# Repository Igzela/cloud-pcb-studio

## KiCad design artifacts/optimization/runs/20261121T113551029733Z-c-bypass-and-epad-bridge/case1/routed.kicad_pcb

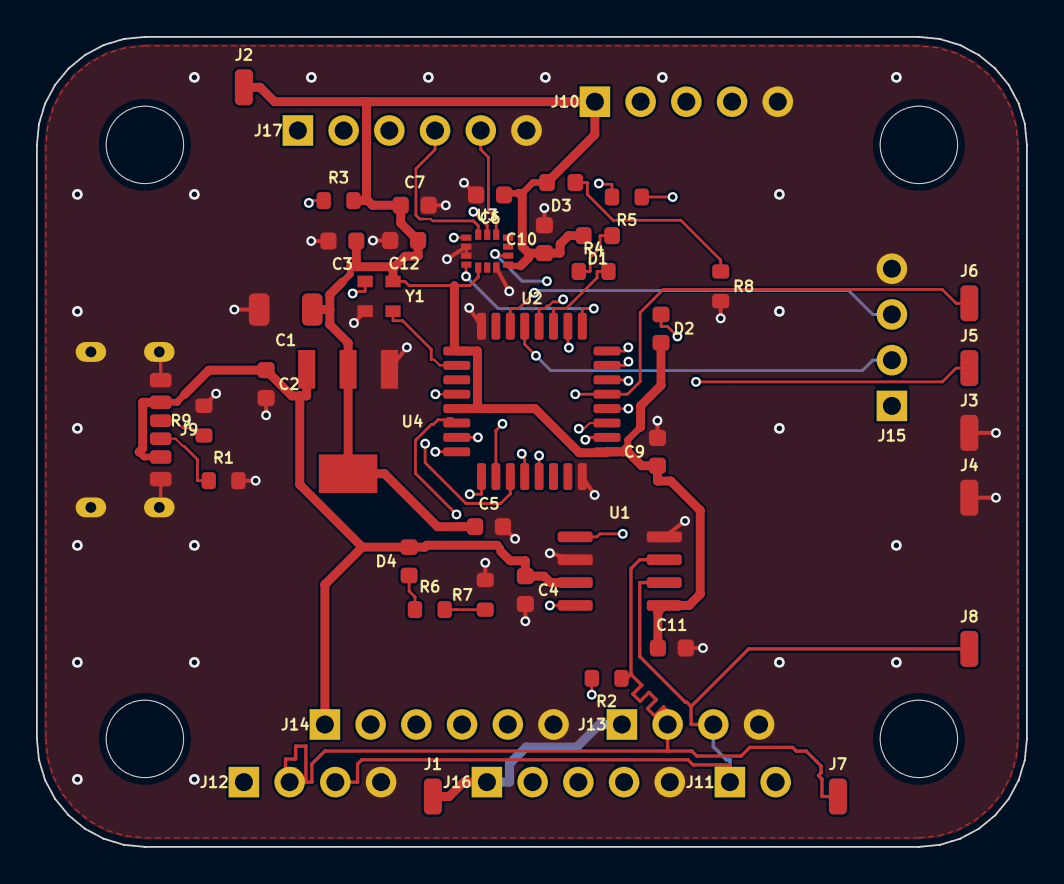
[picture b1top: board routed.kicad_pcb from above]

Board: 4 copper layers, 55.0 x 45.0 mm, 50 parts (0 on the bottom side), 37 nets.

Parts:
C1: 100uF; C_1206_3216Metric
C2: 10uF; C_0603_1608Metric
C3, C4, C5, C6, C9, C10, C11: 100nF; C_0603_1608Metric
C7: 10nF; C_0603_1608Metric
C12: 1uF; C_0603_1608Metric
D1, D2, D3, D4: LED; LED_0603_1608Metric
H1, H2, H3, H4: M_4.3mm; MountingHole_4.3mm
J1, J2, J3, J4, J5, J6, J7, J8: Conn_01x01; SolderWirePad_1x01_SMD_1x2mm
J9: USB_C_Receptacle_PowerOnly_6P; USB_C_Receptacle_GCT_USB4125-xx-x-0190_6P_TopMnt_Horizontal
J10, J16: Conn_01x05; PinHeader_1x05_P2.54mm_Vertical
J11: Conn_01x02; PinHeader_1x02_P2.54mm_Vertical
J12, J13, J15: Conn_01x04; PinHeader_1x04_P2.54mm_Vertical
J14, J17: Conn_01x06; PinHeader_1x06_P2.54mm_Vertical
R1, R9: 5.1K; R_0603_1608Metric
R2: 120R; R_0603_1608Metric
R3: 10k; R_0603_1608Metric
R4, R5: 1k; R_0603_1608Metric
R6, R7, R8: 1K; R_0603_1608Metric
U1: TJA1051T-3; SOIC-8_3.9x4.9mm_P1.27mm
U2: STM32F042K6Tx; LQFP-32_7x7mm_P0.8mm
U3: ASM330LHHXTR; XDCR_ASM330LHHXTR
U4: TLV1117-33; SOT230P700X180-4N
Y1: ASDDV-8.000MHZ-LR-T; Oscillator_SMD_Abracon_ASDMB-4Pin_2.5x2.0mm

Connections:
+3V3: C1.1, C3.1, C5.1, C6.1, C7.1, C9.1, C10.1, C11.1, C12.1, D1.2, D2.2, D3.2, J2.1, J10.1, R3.2, U1.5, U2.1, U2.5, U2.17, U3.5, U3.8, U4.2, Y1.4
+5V: C2.1, C4.1, D4.2, J1.1, J9.A9, J9.B9, J12.1, J13.1, J14.1, J15.1, J16.1, J17.1, U1.3, U4.3
/NRST: J10.4, U2.4
/RCC_OSC_IN: U2.2, Y1.3
/SWCLK: J10.3, U2.24
/SWDIO: J10.2, U2.23
CAN_H: J7.1, J12.2, J13.2, R2.1, U1.7
CAN_L: J8.1, J11.1, J12.3, J13.3, U1.6
CAN_RX: J6.1, U1.4, U2.21
CAN_TX: J5.1, U1.1, U2.22
GND: C1.2, C2.2, C3.2, C4.2, C5.2, C6.2, C7.2, C9.2, C10.2, C11.2, C12.2, J3.1, J4.1, J9.A12, J9.B12, J9.S1, J10.5, J12.4, J13.4, J14.6, J15.4, J16.5, J17.6, R1.2, R7.2, R8.2, R9.2, U1.2, U1.8, U2.16, U2.32, U3.2, U3.3, U3.7, U4.1, Y1.2
GPIO_LED1: R4.2, U2.27
GPIO_LED2: R5.2, U2.28
IMU_CLK: J17.2, U2.11, U3.13
IMU_CS: J17.5, U2.10, U3.12
IMU_IDO: J17.3, U2.12, U3.1
IMU_SDI: J17.4, U2.13, U3.14
unnamed: D1.1, R4.1
unnamed: D2.1, R5.1
unnamed: D3.1, R8.1
unnamed: D4.1, R6.1
unnamed: J9.A5, R9.1
unnamed: J9.B5, R1.1
unnamed: J11.2, R2.2
unnamed: R6.2, R7.1
unnamed: R3.1, Y1.1
TIM1_CH1: J16.2, U2.18
TIM1_CH2: J16.3, U2.19
TIM1_CH3: J16.4, U2.20
TIM2_CH1: U2.25, U3.4
TIM2_CH2: U2.26, U3.9
UART1_RX: J15.3, U2.30
UART1_TX: J15.2, U2.29
UART2_CTS: J14.4, U2.6
UART2_RTS: J14.5, U2.7
UART2_RX: J14.3, U2.9
UART2_TX: J14.2, U2.8

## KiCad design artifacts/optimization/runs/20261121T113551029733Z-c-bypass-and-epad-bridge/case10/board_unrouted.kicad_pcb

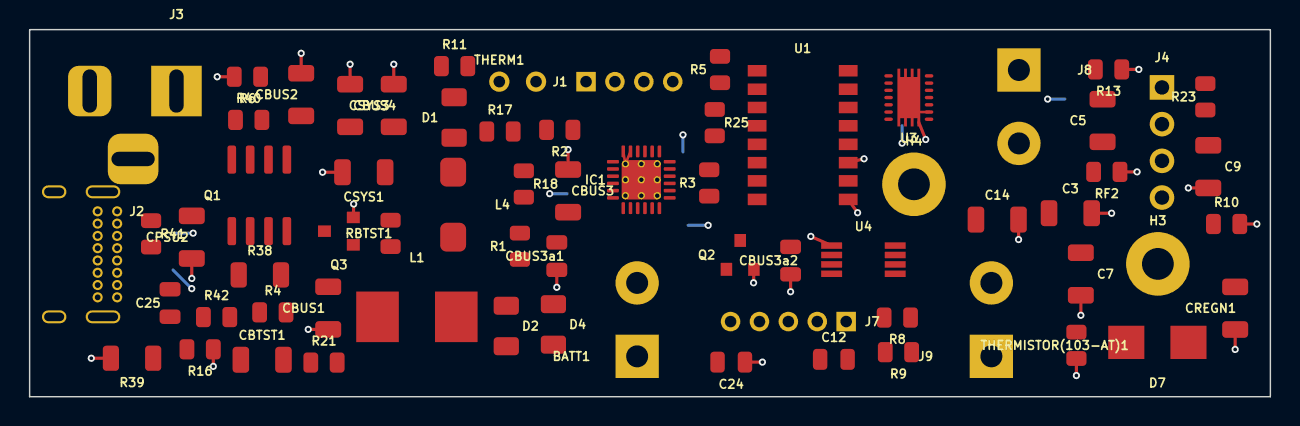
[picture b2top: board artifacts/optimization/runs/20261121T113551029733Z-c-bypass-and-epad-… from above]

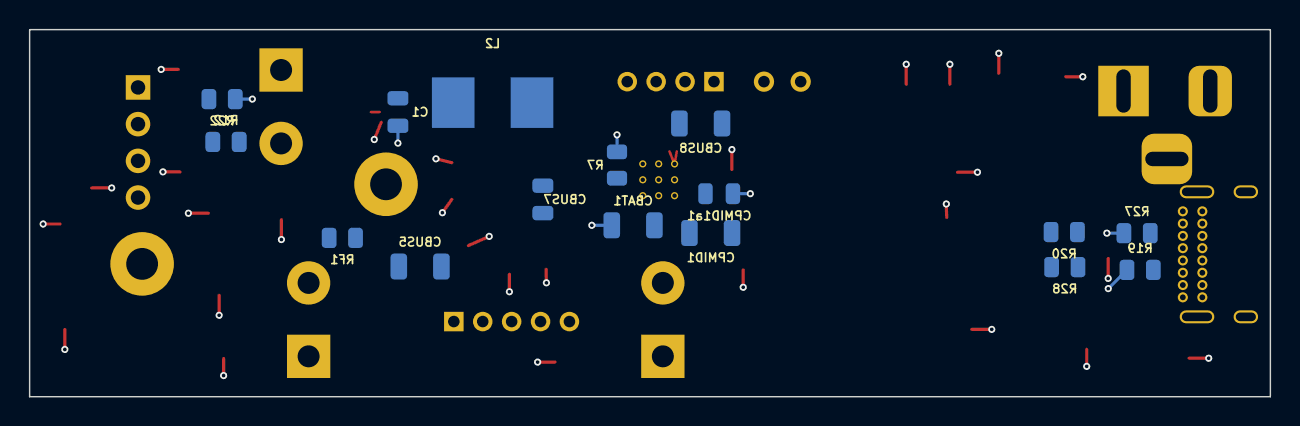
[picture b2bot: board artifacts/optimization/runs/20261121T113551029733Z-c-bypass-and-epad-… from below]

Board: 4 copper layers, 85.9 x 25.4 mm, 84 parts (16 on the bottom side), 50 nets.

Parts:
BATT1: 1s LiPo; TerminalBlock_bornier-2_P5.08mm
C1, C24: 0.1uF; C_0805_2012Metric
C3, C5, C7, C9, C14: 22uF; C_1206_3216Metric
C12: 4.7pF; C_0805_2012Metric
C25: 1nF; C_0805_2012Metric
CBAT1: 10uF; C_1206_3216Metric
CBTST1: 1uF; C_1206_3216Metric
CBUS1, CBUS4: 10uF; C_1206_3216Metric
CBUS2, CBUS3, CBUS5, CBUS8: 1uF; C_1206_3216Metric
CBUS3a1, CBUS3a2, CBUS7: 0.1uF; C_0805_2012Metric
CPMID1: 10uF; C_1206_3216Metric
CPMID1a1: 0.1uF; C_0805_2012Metric
CPSU2: 1uF; C_1206_3216Metric
CREGN1: 1uF; C_1206_3216Metric
CSYS1, CSYS3: 10uF; C_1206_3216Metric
D1, D2, D4: Led; LED_1206_3216Metric
D7: B320; D_SMB
H3: hole; MountingHole_2.2mm_M2_Pad
H4: MountingHole_Pad; MountingHole_2.2mm_M2_Pad
IC1: BQ24193; QFN-24-1EP_4x4mm_P0.5mm_EP2.7x2.7mm_ThermalVias
J1: AudioIN; PinSocket_1x04_P2.00mm_Vertical
J2: USB_C_Receptacle_USB2.0; USB_C_Receptacle_GCT_USB4085
J3: 5-15V / 3-5A; BarrelJack_Horizontal
J4: AudioOUT; PinSocket_1x04_P2.54mm_Vertical
J7: uC host; PinSocket_1x05_P2.00mm_Vertical
J8: 5V 3A; TerminalBlock_bornier-2_P5.08mm
J9: 12V 2A; TerminalBlock_bornier-2_P5.08mm
L1: 2.2uH 4A; L_Bourns_SRP7028A_7.3x6.6mm
L2: 1.5uH 4A; L_Bourns_SRP7028A_7.3x6.6mm
L4: 4.7uH 2A; L_Bourns_SRP5030T
Q1: IRF7404; SOIC-8_3.9x4.9mm_P1.27mm
Q2, Q3: BSS138; SOT-23
R1, R2, R3, R6, R16, R17, R18, R42: 10K; R_0805_2012Metric
R4, R5, R8, R9, R11, R21: 2K2; R_0805_2012Metric
R7: 265; R_0805_2012Metric
R10: 6K8; R_0805_2012Metric
R12, R23: 1M; R_0805_2012Metric
R13: 180K; R_0805_2012Metric
R19, R27: 5K1; R_0805_2012Metric
R20, R28: 56K; R_0805_2012Metric
R22: 270K; R_0805_2012Metric
R25: 150K; R_0805_2012Metric
R38: 120K; R_1206_3216Metric
R39: 49K9; R_1206_3216Metric
R40: 262K; R_0805_2012Metric
R41: 100K; R_0805_2012Metric
RBTST1: R; R_0805_2012Metric
RF1: 820K; R_0805_2012Metric
RF2: 100K; R_0805_2012Metric
THERM1: thermistor; TestPoint_2Pads_Pitch2.54mm_Drill0.8mm
THERMISTOR(103-AT)1: 10K; R_0805_2012Metric
U1: PAM8403-SOP16; SOP-16_4.4x10.4mm_P1.27mm
U3: TPS63020; QFN14-3X4MM
U4: LM2623; VSSOP-8_3.0x3.0mm_P0.65mm

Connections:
5V: C3.1, C5.1, C7.1, C9.1, CBUS3a2.2, J8.2, R12.2, R23.2, U3.4 (VOUT), U3.5 (VOUT_2)
12V: C14.1, D7.1 (K), J9.2, RF1.2, U4.2 (EN), U4.6 (VDD), U4.7 (BOOT)
/CE: IC1.9 (/CE), J7.5, R6.1
/D+: IC1.2 (PSEL), J2.A6 (D+), J2.B6 (D+), R16.2
/D-: IC1.3 (/PG), J2.A7 (D-), J2.B7 (D-), R4.1
/INT: IC1.7 (INT), J7.4, R1.1
/OTG: IC1.8 (OTG), Q2.3 (D), R17.1
/SCL: IC1.5 (SCL), J7.2, R3.1
/SDA: IC1.6 (SDA), J7.3, R2.1
unnamed: BATT1.2, CBAT1.2, IC1.13 (BAT), IC1.14 (BAT)
unnamed: CBTST1.1, RBTST1.1
unnamed: CBUS5.1, R9.1
unnamed: CBUS8.1, R11.1
unnamed: D1.2 (C), R4.2
unnamed: D2.2 (C), R5.2
unnamed: D4.2 (C), R21.1
unnamed: C12.2, D7.2 (A), L4.2, U4.8 (SW)
unnamed: CBTST1.2, IC1.21 (BTST)
unnamed: IC1.10 (ILIM), R7.1
unnamed: CREGN1.2, IC1.22 (REGN), R8.1
unnamed: IC1.4 (STAT), R5.1
unnamed: IC1.19 (SW), IC1.20 (SW), L1.1, RBTST1.2
unnamed: IC1.11 (TS1), IC1.12 (TS2), R8.2, R10.1, THERM1.2, THERMISTOR(103-AT)1.2
unnamed: J1.1, R9.2
unnamed: J1.3, R11.2
unnamed: J1.4, R18.2, U1.5 (MUTE_LOW)
unnamed: J2.A5 (CC1), R20.1, R27.2
unnamed: J2.B5 (CC2), R19.2, R28.1
unnamed: J4.1, U1.3 (-OUT_L)
unnamed: J4.2, U1.1 (+OUT_L)
unnamed: J4.3, U1.16 (+OUT_R)
unnamed: J4.4, U1.14 (-OUT_R)
unnamed: C25.1, Q1.4 (G), Q3.3 (D), R42.2
unnamed: Q2.1 (G), R38.2, R39.1
unnamed: Q3.1 (G), R40.2, R41.1
unnamed: CBUS8.2, U1.7 (IN_L)
unnamed: CBUS5.2, U1.10 (IN_R)
unnamed: CBUS7.2, U1.8 (VREF)
unnamed: C1.1, U3.1 (VINA), U3.12 (EN), U3.13 (PS/SYNC)
unnamed: R12.1, R13.2, R22.2, U3.3 (FB)
unnamed: L2.1, U3.8 (L1), U3.9 (L1_2)
unnamed: L2.2, U3.6 (L2), U3.7 (L2_2)
unnamed: R21.2, R23.1, U3.14 (PG)
unnamed: RF1.1, RF2.2, U4.4 (FB)
unnamed: C12.1, R25.1, U4.3 (FREQ)
PGND: BATT1.1, C1.2, C3.2, C5.2, C7.2, C9.2, C14.2, C24.1, CBAT1.1, CBUS1.1, CBUS2.2, CBUS3.1, CBUS3a1.1, CBUS3a2.1, CBUS4.1, CBUS7.1, CPMID1.1, CPMID1a1.1, CPSU2.1, CREGN1.1, CSYS1.2, CSYS3.2, H3.1, H4.1, IC1.17 (PGND), IC1.18 (PGND), IC1.25 (PGND), J1.2, J2.A1 (GND), J2.A12 (GND), J2.B1 (GND), J2.B12 (GND), J2.S1 (SHIELD), J3.2, J7.1, J8.1, J9.1, Q2.2 (S), Q3.2 (S), R6.2, R7.2, R10.2, R13.1, R16.1, R19.1, R22.1, R27.1, R39.2, R41.2, RF2.1, THERM1.1, THERMISTOR(103-AT)1.1, U1.2 (PGND), U1.9 (NC), U1.11 (GND), U1.15 (PGND), U3.2 (GND), U3.15 (PGND), U3.16 (PGND1), U3.17 (PGND2), U3.18 (PGND3), U3.19 (PGND4), U3.20 (PGND5), U3.21 (PGND6), U3.22 (PGND7), U3.23 (PGND8), U4.1 (PGND), U4.5 (SGND)
POWERBANKOUT: CPMID1.2, CPMID1a1.2, IC1.23 (PMID)
VBUS: C25.2, CBUS3.2, CBUS3a1.2, CPSU2.2, IC1.1 (VBUS), IC1.24 (VBUS), J2.A4 (VBUS), J2.A9 (VBUS), J2.B4 (VBUS), J2.B9 (VBUS), Q1.1 (S), Q1.2 (S), Q1.3 (S), R20.2, R28.2, R42.1
VPSU: J3.1, Q1.5 (D), Q1.6 (D), Q1.7 (D), Q1.8 (D), R38.1, R40.1
VSYS: C24.2, CBUS1.2, CBUS2.1, CBUS4.2, CSYS1.1, CSYS3.1, D1.1 (A), D2.1 (A), D4.1 (A), IC1.15 (SYS), IC1.16 (SYS), L1.2, L4.1, R1.2, R2.2, R3.2, R17.2, R18.1, R25.2, U1.4 (PVDD), U1.6 (VDD), U1.12 (SHDN_LOW), U1.13 (PVDD), U3.10 (VIN), U3.11 (VIN_2)

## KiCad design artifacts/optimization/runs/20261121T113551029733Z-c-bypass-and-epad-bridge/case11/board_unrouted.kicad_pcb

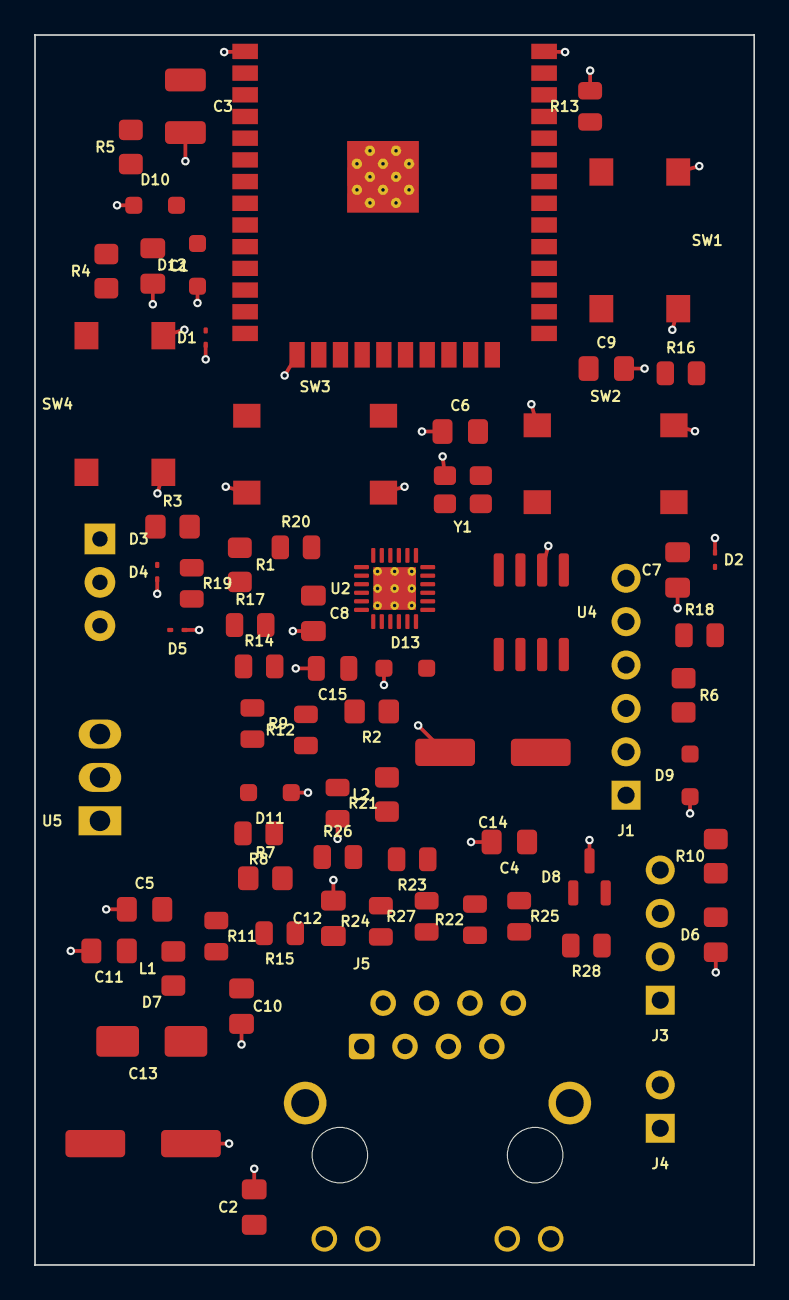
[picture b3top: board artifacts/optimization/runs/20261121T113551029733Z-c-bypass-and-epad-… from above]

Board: 4 copper layers, 42.1 x 72.0 mm, 71 parts (0 on the bottom side), 49 nets.

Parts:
C1, C4: 1u; C_0805_2012Metric_Pad1.18x1.45mm_HandSolder
C2: 10u; C_0805_2012Metric_Pad1.18x1.45mm_HandSolder
C3: 100u; CP_EIA-3528-21_Kemet-B
C5, C7, C10, C11: 100n; C_0805_2012Metric_Pad1.18x1.45mm_HandSolder
C6, C8: 1uF; C_0805_2012Metric_Pad1.18x1.45mm_HandSolder
C9: 470pF; C_0805_2012Metric_Pad1.18x1.45mm_HandSolder
C12: 22nF; C_0805_2012Metric_Pad1.18x1.45mm_HandSolder
C13: 10uF; CP_Elec_6.3x4.9
C14: 1uF; CP_Elec_6.3x4.9
C15: 100nF; C_0805_2012Metric
D1, D2, D4, D5: ESD9B3; D_SOD-923
D3: LED_Dual_KAK; LED_D5.0mm-3
D6: LED; LED_0805_2012Metric_Pad1.15x1.40mm_HandSolder
D7: 1N5819; D_SMA
D8: NUP2105L; SOT-23
D9, D10, D11, D12, D13: PESD3V3L1BA; D_SOD-323_HandSoldering
J1: PROG; PinHeader_1x06_P2.54mm_Vertical
J3: Conn_Left_I2C; PinHeader_1x04_P2.54mm_Vertical
J4: Conn_01x02; PinHeader_1x02_P2.54mm_Vertical
J5: RJ45_Hanrun_HR911105A_Horizontal
L1, L2: BLM21SP181SN1D; R_0805_2012Metric_Pad1.20x1.40mm_HandSolder
R1, R2, R5, R6: 10k; R_0805_2012Metric_Pad1.20x1.40mm_HandSolder
R3, R4: 270R; R_0805_2012Metric_Pad1.20x1.40mm_HandSolder
R7: 0R; R_0805_2012Metric_Pad1.20x1.40mm_HandSolder
R8, R9: 10K; R_0805_2012Metric
R10: 470R; R_0805_2012Metric_Pad1.20x1.40mm_HandSolder
R11, R16, R18, R20: 33R; R_0805_2012Metric
R12: 1K5; R_0805_2012Metric
R13: 4K7; R_0805_2012Metric
R14, R15, R17, R19: 10R; R_0805_2012Metric
R21: 12K1; R_0805_2012Metric
R22, R23, R24, R27: 49R9; R_0805_2012Metric
R25, R26: 270R; R_0805_2012Metric
R28: 120R; R_0805_2012Metric
SW1: RESET; SW_SPST_Omron_B3FS-100xP
SW2: BOOT; SW_SPST_Omron_B3FS-100xP
SW3: Control 1; SW_SPST_Omron_B3FS-100xP
SW4: Control 2; SW_SPST_Omron_B3FS-100xP
U1: ESP32-WROOM-32
U2: LAN8720A; VQFN-24-1EP_4x4mm_P0.5mm_EP2.5x2.5mm_ThermalVias
U4: SN65HVD232; SOIC-8_3.9x4.9mm_P1.27mm
U5: R-78B3.3-2.0; Converter_DCDC_RECOM_R-78B-2.0_THT
Y1: 50MHz; Oscillator_SMD_Abracon_ASE-4Pin_3.2x2.5mm

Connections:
+3.3V: C2.1, C3.1, C6.2, C7.2, C8.1, C9.1, C14.1, C15.1, D13.2 (A2), J1.6, J5.9, J5.12, L1.2, L2.2, R1.2, R2.2, R5.2, R6.2, R7.2, R8.1, R9.1, R10.2, R11.1, R12.1, R15.1, U1.2 (VDD), U2.6 (VDDCR), U2.9 (VDDIO), U4.3 (VCC), U5.3 (OUT), Y1.4 (Vdd)
+24V: D7.2 (A), J3.1
/CAN/CANH: D8.2 (K), J3.2, J4.2, U4.7 (CANH)
/CAN/CANL: D8.1 (K), J3.3, R28.2, U4.6 (CANL)
/CPU/EN: C1.1, D1.2 (A2), D12.2 (A2), J1.5, R1.1, R5.1, SW1.2, U1.3 (EN)
/CPU/LEDA: R4.2, U1.6 (IO34)
/CPU/LEDB: R3.2, U1.7 (IO35)
/CPU/RX: J1.2, U1.34 (RXD0/IO3)
/CPU/TX: J1.3, U1.35 (TXD0/IO1)
/Ethernet/PHY_L1: R25.1, U2.3 (LED1/REGOFF)
/Ethernet/PHY_L2: R26.1, U2.2 (LED2/~INTSEL)
/Ethernet/PHY_RD+: J5.3 (RD+), R24.2, U2.23 (RXP)
/Ethernet/PHY_RD-: J5.6 (RD-), R27.2, U2.22 (RXN)
/Ethernet/PHY_TD+: J5.1 (TD+), R22.2, U2.21 (TXP)
/Ethernet/PHY_TD-: J5.2 (TD-), R23.2, U2.20 (TXN)
CTRL1: D4.2 (A2), D10.2 (A2), R8.2, SW3.1
CTRL2: D5.2 (A2), D11.2 (A2), R9.2, SW4.1
ETH_CRS_DV: R14.1, U1.12 (IO27)
ETH_EN_CLK: R13.1, U1.28 (IO17), Y1.1 (EN)
ETH_MDC: U1.37 (IO23), U2.13 (MDC)
ETH_MDIO: R12.2, U1.30 (IO18), U2.12 (MDIO)
ETH_RXCLK: C4.1, D2.2 (A2), D9.2 (A2), J1.4, R2.1, R6.1, R16.1, R18.1, SW2.2, U1.25 (IO0)
ETH_RXD0: R19.1, U1.10 (IO25)
ETH_RXD1: R17.1, U1.11 (IO26)
ETH_TXD0: U1.31 (IO19), U2.17 (TXD0)
ETH_TXD1: U1.36 (IO22), U2.18 (TXD1)
ETH_TXEN: U1.33 (IO21), U2.16 (TXEN)
GND: C1.2, C2.2, C3.2, C4.2, C5.1, C6.1, C7.1, C8.2, C9.2, C10.2, C11.2, C12.2, C13.2, C14.2, C15.2, D1.1 (A1), D2.1 (A1), D4.1 (A1), D5.1 (A1), D6.1 (K), D8.3 (A), D9.1 (A1), D10.1 (A1), D11.1 (A1), D12.1 (A1), D13.1 (A1), J1.1, J3.4, J5.8, J5.SH, R13.2, R21.2, SW1.1, SW2.1, SW3.2, SW4.2, U1.1 (GND), U1.15 (GND), U1.38 (GND), U1.39 (GND), U2.25 (VSS), U4.2 (GND), U5.2 (GND), Y1.2 (GND)
unnamed: D3.2 (A), R7.1
unnamed: D3.1 (K1), R4.1
unnamed: D3.3 (K2), R3.1
unnamed: D6.2 (A), R10.1
unnamed: C13.1, D7.1 (K), U5.1 (IN)
unnamed: J4.1, R28.1
unnamed: J5.10, R26.2
unnamed: J5.11, R25.2
unnamed: C12.1, J5.4 (TCT), J5.5 (RCT), L2.1, R22.1, R23.1, R24.1, R27.1
unnamed: R14.2, U2.11 (CRS_DV/MODE2)
unnamed: R21.1, U2.24 (RBIAS)
unnamed: R19.2, U2.8 (RXD0/MODE0)
unnamed: R17.2, U2.7 (RXD1/MODE1)
unnamed: R15.2, U2.10 (RXER/PHYAD0)
unnamed: C10.1, C11.1, L1.1, U2.1 (VDD2A), U2.19 (VDD1A)
unnamed: R20.1, U2.5 (XTAL1/CLKIN)
unnamed: R18.2, U2.14 (~INT/REFCLKO)
unnamed: R16.2, R20.2, Y1.3 (OUT)
PHY_RST: C5.2, R11.2, U2.15 (~RST)
RXCAN: U1.18 (SWP/SD3), U4.4 (R)
TXCAN: U1.17 (SHD/SD2), U4.1 (D)

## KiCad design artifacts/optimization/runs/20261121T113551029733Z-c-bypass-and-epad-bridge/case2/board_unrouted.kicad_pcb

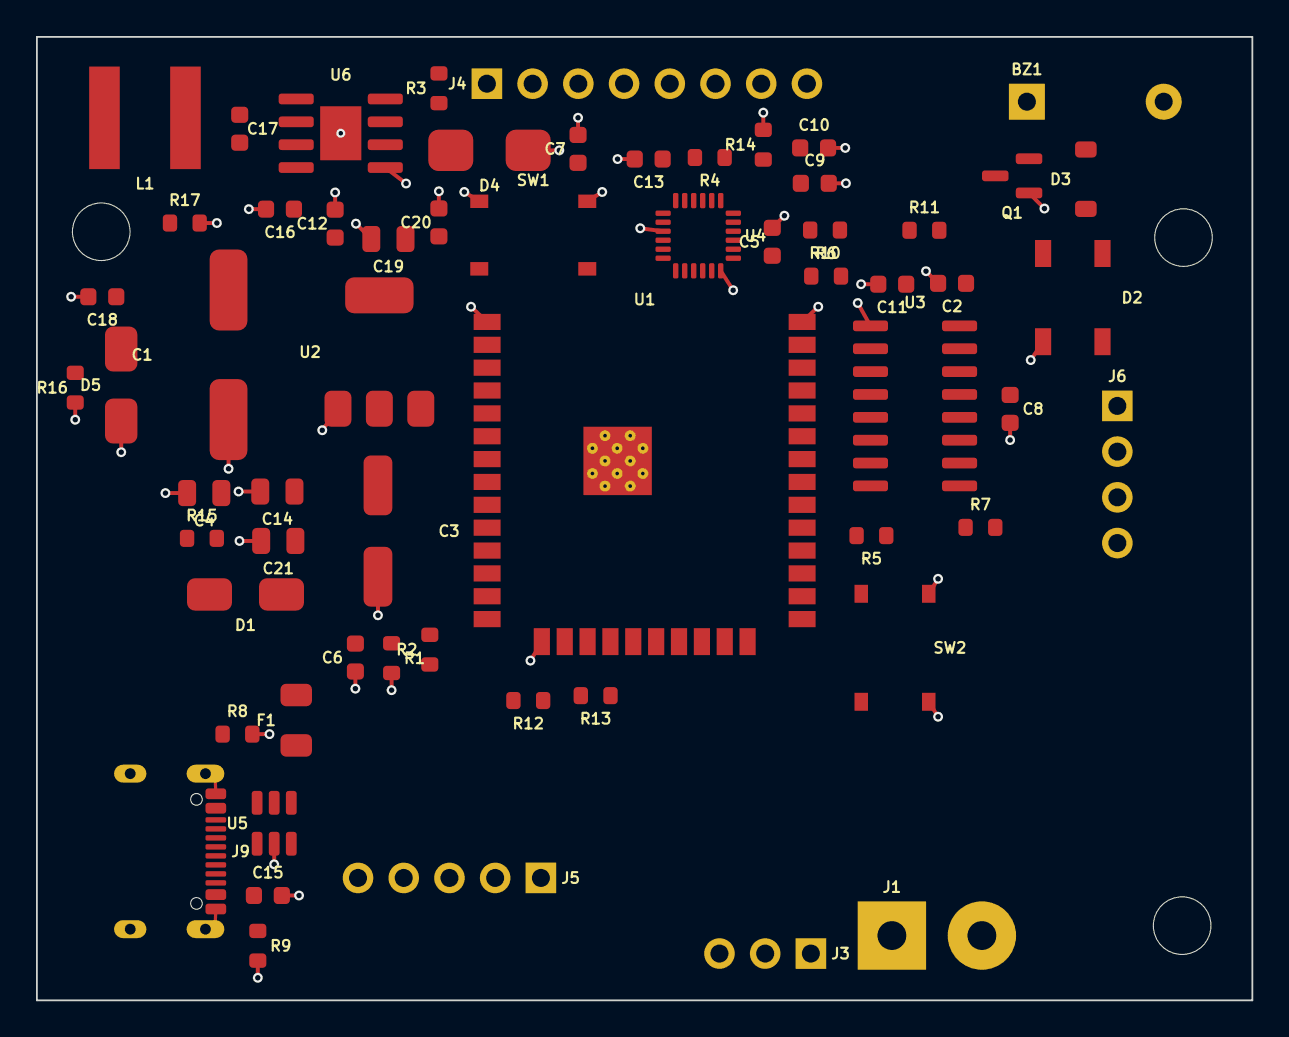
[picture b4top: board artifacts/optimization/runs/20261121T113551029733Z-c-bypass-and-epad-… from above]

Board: 4 copper layers, 67.5 x 53.5 mm, 64 parts (0 on the bottom side), 50 nets.

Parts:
BZ1: Buzzer; Buzzer_12x9.5RM7.6
C1: 100uF 35V; C_Elec_8x10.2
C2, C5, C6, C7, C8, C9, C12, C13, C15, C16, C17, C20: 100nF; C_0603_1608Metric
C3: 100uF 16V; C_Elec_6.3x5.8
C4: 10uF 16V; C_0805_2012Metric
C10: 2.2nF; C_0603_1608Metric
C11: 10nF; C_0603_1608Metric
C14: 22uF; C_0805_2012Metric
C18: 220p; C_0603_1608Metric
C19, C21: 10uF; C_0805_2012Metric
D1: SS34; D_SMA
D2: WS2812B; LED_WS2812B_PLCC4_5.0x5.0mm_P3.2mm
D3: 1N4148; D_SOD-123
D4: SM6T24A; D_SMB
D5: D_Schottky; D_SMA
F1: 500mA; Fuse_1206_3216Metric
H1, H2, H3: M_3.2mm; MountingHole_3.2mm
J1: Battery XT30; AMASS_XT30U-M_1x02_P5.0mm_Vertical
J3: IBUS/SBUS RECIEVER; PinHeader_1x03_P2.54mm_Vertical
J4: PWM RECIEVER; PinHeader_1x08_P2.54mm_Vertical
J5: MOTOR OUT; PinHeader_1x05_P2.54mm_Vertical
J6: GPS; PinHeader_1x04_P2.54mm_Vertical
J9: USB_C_Receptacle_USB2.0_16P; USB_C_Receptacle_GCT_USB4105-xx-A_16P_TopMnt_Horizontal
L1: 22u; L_Sunlord_SWPA6028S
Q1: 2N3904; SOT-23
R1: 22k; R_0603_1608Metric
R2, R3: 100k; R_0603_1608Metric
R4, R5: 10k; R_0603_1608Metric
R6: 1k; R_0603_1608Metric
R7: 330k; R_0603_1608Metric
R8, R9: 5.1k; R_0603_1608Metric
R10, R11: 4.7k; R_0603_1608Metric
R12, R13: 22; R_0603_1608Metric
R14: 200k; R_0603_1608Metric
R15: 211k; R_0603_1608Metric
R16: 40.2k; R_0603_1608Metric
R17: 68.1k; R_0603_1608Metric
SW1: RESET; SW_Push_1P1T_XKB_TS-1187A
SW2: BOOT; SW_Push_1P1T_XKB_TS-1187A
U1: ESP32-WROOM-32E; ESP32-WROOM-32D
U2: AMS1117-3.3; SOT-223-3_TabPin2
U3: CH340C; SOIC-16_3.9x9.9mm_P1.27mm
U4: MPU-6050; InvenSense_QFN-24_4x4mm_P0.5mm
U5: USBLC6-2SC6; SOT-23-6
U6: MP1584EN; SOIC-8-1EP_3.9x4.9mm_P1.27mm_EP2.29x3mm

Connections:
+3.3V: C2.1, C4.1, C5.1, C7.1, C11.1, C12.1, C13.1, J6.1, R4.1, R5.1, R10.1, R11.1, U1.2, U2.2, U3.16, U4.8, U4.13
+3V3: BZ1.2, D2.1, D3.1
+5V: C3.1, C14.1, C19.1, C20.1, C21.1, F1.2, J3.2, J4.7, L1.1, R15.2, U2.3
+BATT: D1.2, J1.1, R2.1
/VIN: C1.2, C16.1, D1.1, D4.2, R3.1, U6.7
/usb+: J9.A6, J9.B6, U5.1
/usb-: J9.A7, J9.B7, U5.3
/usb_esd-: R13.2, U5.4
/usb_mcu+: R12.1, U3.5
/usb_mcu-: R13.1, U3.6
BUZZER: R6.1, U1.16
CH1: J4.1, U1.8
CH2: J4.2, U1.9
CH3: J4.3, U1.7
CH4: J4.4, U1.30
CH5: J4.5, U1.31
CH6: J4.6, U1.37
ESC1: J5.1, U1.10
ESC2: J5.2, U1.11
ESC3: J5.3, U1.12
ESC4: J5.4, U1.13
GND: C1.1, C2.2, C3.2, C4.2, C5.2, C6.1, C7.2, C8.2, C9.2, C10.2, C11.2, C12.2, C13.2, C14.2, C15.2, C16.2, C18.2, C19.2, C20.2, C21.2, D2.3, D4.1, D5.1, J1.2, J3.3, J4.8, J5.5, J6.2, J9.A1, J9.A12, J9.B1, J9.B12, J9.S1, Q1.1, R1.2, R8.2, R9.2, R14.2, R16.1, R17.2, SW1.1, SW2.1, U1.1, U1.15, U1.38, U1.39, U2.1, U3.1, U4.9, U4.11, U4.18, U5.2, U6.5, U6.9
GPS RX: J6.4, U1.28
GPS TX: J6.3, U1.29
INT: U1.6, U4.12
LED_STAT: R7.1, U1.26
unnamed: BZ1.1, D3.2, Q1.2
unnamed: D2.4, R7.2
unnamed: C17.2, D5.2, L1.2, U6.1
unnamed: J9.A5, R8.1
unnamed: J9.B5, R9.1
unnamed: Q1.3, R6.2
unnamed: R12.2, U5.6
unnamed: R4.2, SW1.2, U1.3
unnamed: R5.2, SW2.2, U1.25
unnamed: C8.1, U3.4
unnamed: C10.1, U4.20
unnamed: C9.1, U4.10
unnamed: C15.1, F1.1, J9.A4, J9.A9, J9.B4, J9.B9, U5.5
unnamed: C17.1, U6.8
unnamed: C18.1, R17.1, U6.3
unnamed: R3.2, U6.2
unnamed: R15.1, R16.2, U6.4
unnamed: R14.1, U6.6
RX: U1.34, U3.2
SCL: R11.2, U1.36, U4.23
SDA: R10.2, U1.33, U4.24
SENOR_VP: C6.2, R1.1, R2.2, U1.4
TX: U1.35, U3.3
iBUS/SBUS RX: J3.1, U1.27

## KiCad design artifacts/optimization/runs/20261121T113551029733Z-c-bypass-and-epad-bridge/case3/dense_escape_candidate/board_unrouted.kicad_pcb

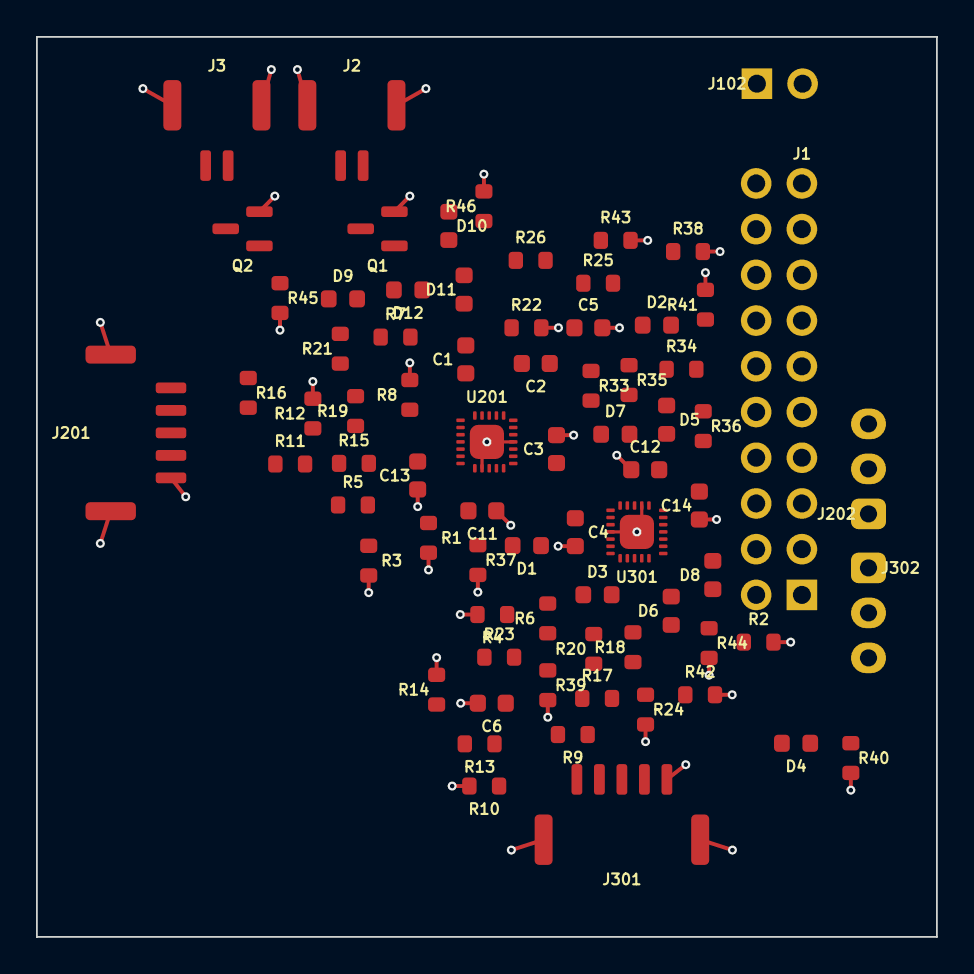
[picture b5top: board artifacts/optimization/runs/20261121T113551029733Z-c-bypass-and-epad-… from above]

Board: 4 copper layers, 50.0 x 50.0 mm, 74 parts (0 on the bottom side), 57 nets.

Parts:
C1, C2: 0u22; C_0603_1608Metric
C3, C4: 2u2; C_0603_1608Metric
C5, C6: 1n; C_0603_1608Metric
C11, C12: 10u; C_0603_1608Metric
C13, C14: 0u1; C_0603_1608Metric
D1, D2, D3, D4, D5, D6, D7, D8, D9, D10: LED; D_0603_1608Metric
D11, D12: D_0603_1608Metric
J1: Conn_02x10_Odd_Even; PinSocket_2x10_P2.54mm_Vertical
J2, J3: Conn_01x02; JST_GH_BM02B-GHS-TBT_1x02-1MP_P1.25mm_Vertical
J102: Conn_01x02; 2-Pin_PSK
J201, J301: Hall; JST_GH_BM05B-GHS-TBT_1x05-1MP_P1.25mm_Vertical
J202, J302: Motor; JST_XH_B3B-XH-A_1x03_P2.50mm_Vertical
Q1, Q2: BSS138; SOT-23
R1, R2: 10k; R_0603_1608Metric
R3, R4, R5, R6, R7, R8, R9, R10, R11, R12, R13, R14: 100k; R_0603_1608Metric
R15, R16, R17, R18, R19, R20, R21, R22, R23, R24, R37, R38, R39, R40, R41, R42, R43, R44, R45, R46: 1k; R_0603_1608Metric
R25, R26: 10; R_0603_1608Metric
R33, R34, R35, R36: 5.1k; R_0603_1608Metric
U201, U301: MCT8314ZH; WQFN24_RRW_TEX_new

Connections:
+3V3: J1.19, R33.1, R34.1, R35.1, R36.1
+6V: C1.2, C2.2, C11.2, C12.2, C13.2, C14.2, D9.2, D10.2, D11.1, D12.1, J1.17, J2.1, J3.1, J102.1, U201.8, U301.8
/Left Driver/+5V: C3.1, J201.4, R5.1, R7.1, R11.1, R15.1, R16.1, R19.1, R21.1, U201.15
/Left Driver/ADVANCE: R3.1, R5.2, U201.1
/Left Driver/CP: C1.1, D1.2, U201.7
/Left Driver/FGSEL: R7.2, R8.1, U201.24
/Left Driver/HALL_U: J201.2, R15.2, U201.17
/Left Driver/HALL_V: J201.3, R16.2, U201.19
/Left Driver/HALL_W: J201.5, R19.2, U201.21
/Left Driver/HNA: C5.1, R21.2, R22.1, U201.18, U201.20, U201.22
/Left Driver/ILIM: R1.1, U201.3
/Left Driver/MODE: R11.2, R12.1, U201.23
/Left Driver/U: J202.1, U201.10
/Left Driver/V: J202.2, U201.11
/Left Driver/W: J202.3, U201.12
/M1_BRAKE: D3.2, J1.1, U201.4
/M1_DIR: D5.2, J1.3, U201.2
/M1_FAULT: J1.7, R35.2, U201.13
/M1_PWM: D7.2, J1.5, U201.5
/M1_TACHO: J1.9, R33.2, U201.6
/M2_BRAKE: D4.2, J1.2, U301.4
/M2_DIR: D6.2, J1.4, U301.2
/M2_FAULT: J1.8, R36.2, U301.13
/M2_PWM: D8.2, J1.6, U301.5
/M2_TACHO: J1.10, R34.2, U301.6
/Right Driver/+5V: C4.1, J301.4, R6.1, R9.1, R13.1, R17.1, R18.1, R20.1, R23.1, U301.15
/Right Driver/ADVANCE: R4.1, R6.2, U301.1
/Right Driver/CP: C2.1, D2.2, U301.7
/Right Driver/FGSEL: R9.2, R10.1, U301.24
/Right Driver/HALL_U: J301.2, R17.2, U301.17
/Right Driver/HALL_V: J301.3, R18.2, U301.19
/Right Driver/HALL_W: J301.5, R20.2, U301.21
/Right Driver/HNA: C6.1, R23.2, R24.1, U301.18, U301.20, U301.22
/Right Driver/ILIM: R2.1, U301.3
/Right Driver/MODE: R13.2, R14.1, U301.23
/Right Driver/U: J302.1, U301.10
/Right Driver/V: J302.2, U301.11
/Right Driver/W: J302.3, U301.12
/WAVEARM_PWM_1: J1.13, R25.2
/WAVEARM_PWM_2: J1.15, R26.2
/~M1_SLEEP: J1.11, U201.14
/~M2_SLEEP: J1.12, U301.14
GND: C3.2, C4.2, C5.2, C6.2, C11.1, C12.1, C13.1, C14.1, J1.20, J2.MP, J3.MP, J102.2, J201.1, J201.MP, J301.1, J301.MP, Q1.2, Q2.2, R1.2, R2.2, R3.2, R4.2, R8.2, R10.2, R12.2, R14.2, R22.2, R24.2, R37.2, R38.2, R39.2, R40.2, R41.2, R42.2, R43.2, R44.2, R45.2, R46.2, U201.9, U201.16, U201.25, U301.9, U301.16, U301.25
unnamed: D1.1, R37.1
unnamed: D2.1, R38.1
unnamed: D3.1, R39.1
unnamed: D4.1, R40.1
unnamed: D5.1, R41.1
unnamed: D6.1, R42.1
unnamed: D7.1, R43.1
unnamed: D8.1, R44.1
unnamed: D9.1, R45.1
unnamed: D10.1, R46.1
unnamed: D11.2, J2.2, Q1.3
unnamed: D12.2, J3.2, Q2.3
unnamed: Q1.1, R25.1
unnamed: Q2.1, R26.1
